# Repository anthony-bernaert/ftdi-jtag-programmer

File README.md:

# FTDI-based JTAG Programmer for FPGAs
This JTAG programmer board is based on an FTDI chip and supports Lattice, AMD (Xilinx), Intel (Altera) FPGAs, and probably more. It allows those devices to be programmed and debugged over USB through their regular toolchains.

The board also provides a separate UART port for general-purpose serial communication between a PC application and any other board.

If you work with a lot of different FPGAs, this solution can be used as a universal, cost-effective replacement for most of your vendor-specific JTAG cables.

## Features
- Based on the FT2232H chip
- USB-C connector
- On-board resettable fuse to protect your host's USB port
- 1 JTAG port
  - Programs and debugs Lattice, AMD/Xilinx, Altera/Intel, and probably also other FPGAs through their respective toolchains
  - Standard 2 mm Xilinx 2x7 header connector
  - Also has a 6-pin 2.54 mm header for use with jumper wires
  - Voltage reference input pin configures the I/O voltage (2.5-5V)
  - An LED indicates presence of an external VREF voltage
- 1 UART port
  - Generic serial communication through virtual COM port
  - 6-pin 2.54 mm header, pinout compatible with FTDI's TTL-232R cables
  - Configurable 5V output or voltage reference input (2.5-5V) (*)
  - An LED indicates presence of an external VREF voltage
- Buffered I/O pins with surge protection
  - Outputs are current-limited
  - Inputs are 5V tolerant
- For Xilinx/AMD and Lattice, only the standard FTDI software drivers are needed
 
(*) These are mounting variations, so to be decided during PCB assembly.

## Build overview

This board was designed using KiCad 7.0.2.

Navigate to the releases section to obtain the latest production files and schematic. The BOM contains references to LCSC parts, so that you can easily order PCB assemblies at e.g. JLCPCB.

Files for 3D printing an optional enclosure are also provided. The enclosure is recommended to prevent accidental shorts during use.

It consists of a top and bottom part, which slide in horizontally; no screws or glue are necessary. For resilience and visibility of the LEDs, it is recommended to print it in a translucent PETG material.

## How to use
### First-time configuration
Install FTDI's VCP/D2XX drivers for your operating system [from their website](https://ftdichip.com/drivers/).

Also install [FT_PROG](https://ftdichip.com/utilities/#ft_prog). This utility will be used to initialize the EEPROM of the board with the correct settings.

Now you can choose to either initialize the EEPROM using FT_PROG or directly flash the device using an existing EEPROM dump.

>[!TIP]
>The most versatile solution is to flash the EEPROM with the Digilent SMT1 dump. The programmer then works simultaneously for Vivado, ISE, Diamond and Quartus (details in the [Xilinx ISE section](#xilinx-ise)).
>
>However, for the very first startup of your board, please try to write the following settings using the FT_PROG utility. This way, you can make sure that your hardware and drivers are working properly.

When FT_PROG is installed, connect the board to your PC. At this point, the green PWREN LED should be on: this means the PC has enumerated the device. If this is not the case, see the [Troubleshooting Guide](TROUBLESHOOTING.md).

In FT_PROG, scan and parse the connected devices. Configure your board as follows:
- Port A
  - Set the hardware mode to "245 FIFO"
  - Set the driver to D2XX Direct
- Port B
  - Set the hardware mode to "RS232 UART"
  - Set the driver to Virtual COM Port

Finally, program this configuration into the EEPROM. Depending on the vendor of the FPGA you want to program, a few additional steps might be needed. These are described below.

### Lattice
To use the programmer with Lattice devices, just open the programming software such as Diamond Programmer and select the 'HW-USBN-2B (FTDI)' option as the cable type.

Diamond programmer can use any FTDI device configured in D2XX mode. No additional configuration is needed.

>[!NOTE]
>This programmer is known to work with Diamond Programmer software - other tools, such as Radiant Programmer, have not been tested yet.

### AMD/Xilinx Vivado
For AMD/Xilinx tools, the software looks for a Xilinx signature in the FTDI device EEPROM. Once this is done, the programmer appears as any other official programming cable in Vivado Hardware Manager. To add the signature, you have two options: either write a recognized EEPROM dump to the device (recommended), or use AMD's `program_ftdi` utility.

The recommended way is to use the Digilent SMT1 dump; refer to the [Xilinx ISE section](#xilinx-ise) on how to do this.

If you really want to do it AMD's way: recent Vivado versions (starting from 2022) contain the `program_ftdi` tool that configures FTDI chips as AMD/Xilinx JTAG programmers. Running this utility (once) will make the programmer work with Vivado. You can execute it from the TCL console, e.g. in the Hardware Manager of Vivado. Run a command similar to this one:
```
program_ftdi -write -ftdi FT2232H -serial 0ABC01 -vendor "my vendor co" -board "my board" -desc "my product desc"
```
Note that the 'serial' parameter must match the serial number generated by FT_PROG. After programming, the programmer should show up in the Hardware Manager of Vivado.

>[!WARNING]
>Unfortunately, it seems that the `program_ftdi` is broken in Vivado 2024.1. If you see it complaining about missing DLLs while trying to program, try using an older version of Vivado, e.g. 2023.2, which is known to work.

### Xilinx ISE
To use this programmer with Xilinx' older ISE toolchain, you'll need to flash the EEPROM to mimick a legacy Digilent SMT1 device. You will find the required EEPROM dump on [dragonlock2's ftdi_dumps repository](https://github.com/dragonlock2/ftdi_dumps?tab=readme-ov-file). Afterwards, the device appears as a Digilent SMT1 device in the cable setup window.

Note that this dump has the advantage that you can make the programmer work simultaneously for Vivado, ISE, Diamond and Quartus, turning your programmer in an (at least) 4-in-1 solution!

>[!TIP]
>Writing the EEPROM configuration can be done using the (Linux) utility `ftdi_eeprom` or my own [FTDI EEPROM cloning tool](https://github.com/anthony-bernaert/ftdi-cloner).

Once the EEPROM is programmed, the cable appears as a Digilent USB JTAG cable:

### Altera/Intel
For Quartus software to work with FT2232HL devices, one option is to add a library file to your Quartus installation directory. You'll find a ready-made DLL (if you're on Windows) [here](https://github.com/anthony-bernaert/jtag-mpsse-blaster). This is a fork of an open-source solution that adds FTDI MPSSE support to Quartus Programmer/Signal Tap. Linux is also supported, though I did not test this.

After installing the .dll/.so file, the JTAG programmer board should show up in the available hardware list of Quartus and your FPGA is ready to be programmed:

If you don't like modifying your Quartus installation manually, an alternative solution is to configure the USB device as an 'Arrow USB Blaster'. You will find the required EEPROM dump on [dragonlock2's ftdi_dumps repository](https://github.com/dragonlock2/ftdi_dumps?tab=readme-ov-file).

>[!TIP]
>Writing the EEPROM configuration can be done using the (Linux) utility `ftdi_eeprom` or my own [FTDI EEPROM cloning tool](https://github.com/anthony-bernaert/ftdi-cloner).

In this case, you also need to install the [Arrow USB Blaster driver](https://shop.trenz-electronic.de/en/Download/?path=Trenz_Electronic/Software/Drivers/Arrow_USB_Programmer). After this, your FTDI programmer should appear in the hardware list of Quartus Programmer and your FPGA is ready to be programmed.

## Troubleshooting
If you experience problems while using this board, check out the [Troubleshooting Guide](TROUBLESHOOTING.md).

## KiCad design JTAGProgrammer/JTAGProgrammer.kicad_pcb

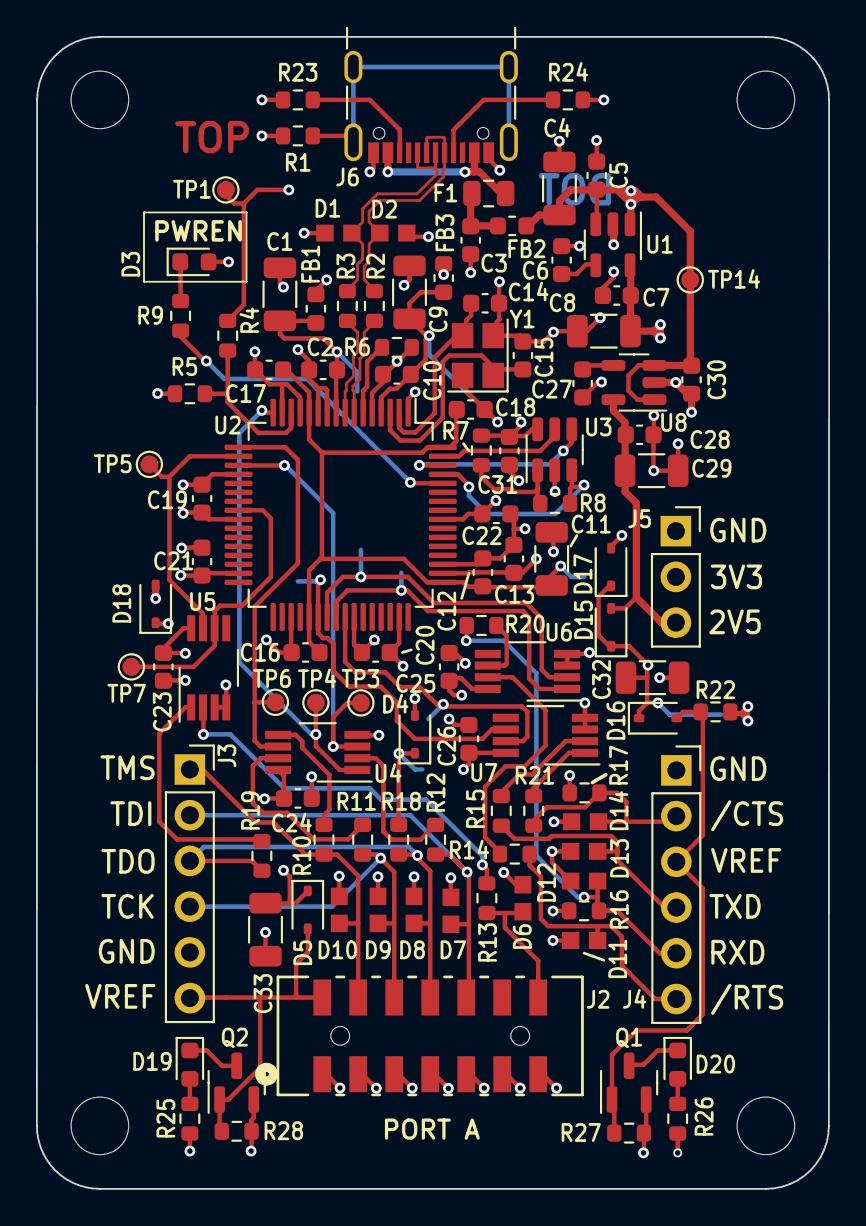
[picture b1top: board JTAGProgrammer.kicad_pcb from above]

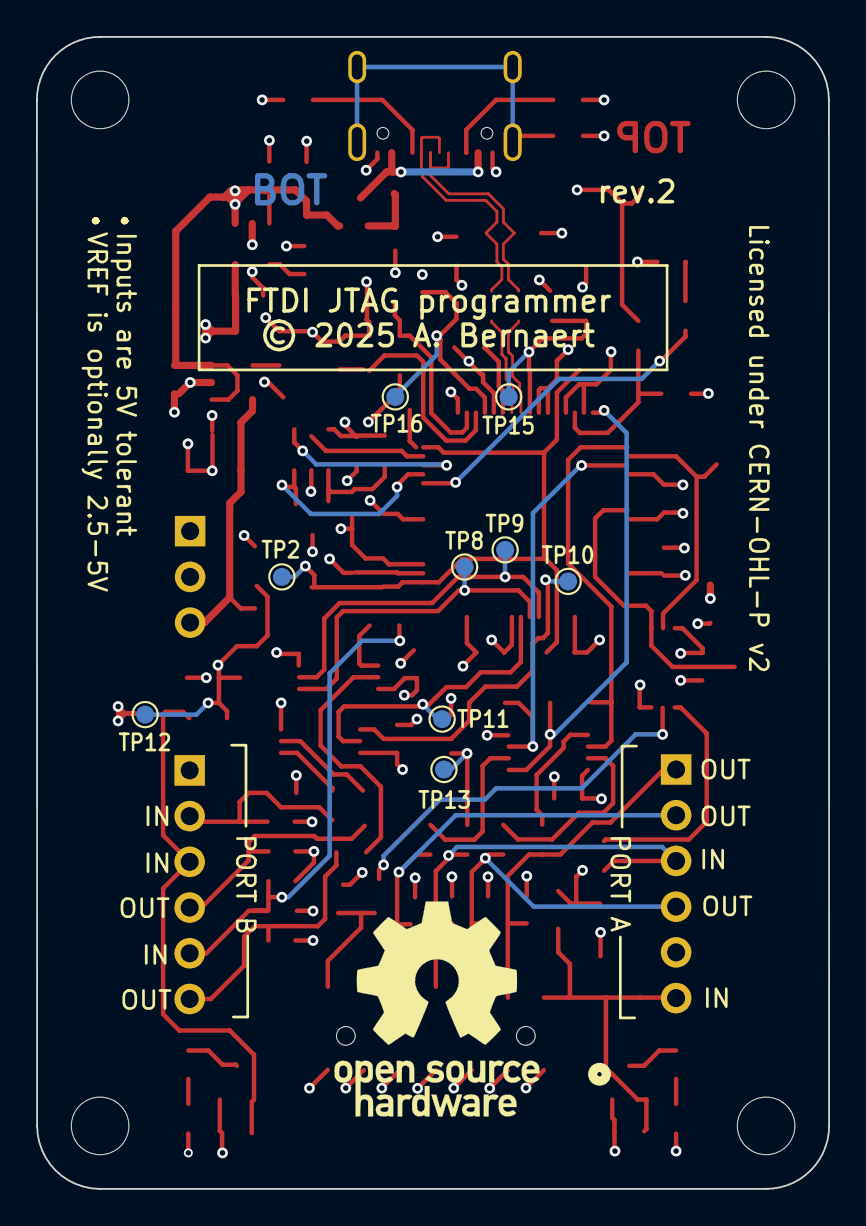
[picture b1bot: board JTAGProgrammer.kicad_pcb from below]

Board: 4 copper layers, 44.0 x 64.0 mm, 121 parts (9 on the bottom side), 63 nets.

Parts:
C1, C4, C8, C9, C11, C29, C32, C33: 4.7u; C_1206_3216Metric
C2, C5, C7, C10, C12, C13, C16, C17, C18, C19, C20, C21, C22, C23, C24, C25, C26, C28, C30, C31: 100n; C_0603_1608Metric
C3, C6, C27: 10n; C_0603_1608Metric
C14, C15: 10p; C_0603_1608Metric
D1, D2, D6, D7, D8, D9, D10, D11, D12, D13, D14: PGB1010603MR; DIOC1608X36N
D3, D19, D20: LED; LED_0603_1608Metric
D4, D5, D15, D16, D17, D18: CUS520,H3F; D_SOD-323
F1: 0805L075SLYR; Fuse_0805_2012Metric
FB1, FB2, FB3: BLM18AG601SN1D; L_0603_1608Metric
H1, H2, H3, H4: MountingHole; MountingHole_3.2mm_M3
J2: 878325623; CONN_87832-5623_MOL
J3, J4: Conn_01x06; PinSocket_1x06_P2.54mm_Vertical
J5: Conn_01x03; PinSocket_1x03_P2.54mm_Vertical
J6: USB_C_Receptacle_USB2.0; USB_C_Receptacle_GCT_USB4105-xx-A_16P_TopMnt_Horizontal
Q1, Q2: BSS123; SOT-23
R1, R22: 0R; R_0603_1608Metric
R2, R3: 10R; R_0603_1608Metric
R4: 15K; R_0603_1608Metric
R5, R7, R16, R17, R18, R27, R28: 10K; R_0603_1608Metric
R6: 12K; R_0603_1608Metric
R8: 2.2K; R_0603_1608Metric
R9, R25, R26: 100R; R_0603_1608Metric
R10, R11, R12, R13, R14, R15, R19, R20, R21: 150R; R_0603_1608Metric
R23, R24: 5K1; R_0603_1608Metric
TP1, TP2, TP3, TP4, TP5, TP6, TP7, TP8, TP9, TP10, TP11, TP12, TP13, TP14, TP15, TP16: TestPoint; TestPoint_Pad_D1.0mm
U1: LP2985-3.3; SOT-23-5
U2: FT2232HL; LQFP-64_10x10mm_P0.5mm
U3: 93LC56B; SOT-23-6
U4, U5, U6, U7: 74LVC3G17; VSSOP-8_3.0x3.0mm_P0.65mm
U8: LP2985-2.5; SOT-23-5
Y1: RH100-12.000-10-3030-TR; Crystal_SMD_3225-4Pin_3.2x2.5mm

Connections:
+1V8: C11.1, C12.1, C16.1, C17.1, C18.1, TP2.1, U2.12 (VCORE), U2.37 (VCORE), U2.49 (VREGOUT), U2.64 (VCORE)
+2V5: C28.1, C29.1, D4.2 (A), D15.2 (A), J5.3, U8.5 (VOUT)
+3V3: C7.1, C8.1, C13.1, C19.1, C20.1, C21.1, C22.1, C31.1, D3.2 (A), D17.2 (A), D18.2 (A), FB1.1, FB3.1, J5.2, R7.2, R25.1, R26.1, U1.5 (VOUT), U2.20 (VCCIO), U2.31 (VCCIO), U2.42 (VCCIO), U2.50 (VREGIN), U2.56 (VCCIO), U3.6 (VCC)
/FTDI/FTDI_D+: R3.2, U2.8 (DP)
/FTDI/FTDI_D-: R2.2, U2.7 (DM)
/FTDI/JTAG_SRST: TP7.1, U2.24 (ADBUS7), U5.6
/FTDI/JTAG_TCK: TP4.1, U2.16 (ADBUS0), U4.1
/FTDI/JTAG_TDI: TP6.1, U2.17 (ADBUS1), U4.6
/FTDI/JTAG_TDO: TP5.1, U2.18 (ADBUS2), U5.7
/FTDI/JTAG_TMS: TP3.1, U2.19 (ADBUS3), U4.3
/FTDI/UART_CTS: TP11.1, U2.41 (BDBUS3), U7.7
/FTDI/UART_RTS: TP8.1, U2.40 (BDBUS2), U6.1
/FTDI/UART_RXD: TP9.1, U2.39 (BDBUS1), U6.2
/FTDI/UART_TXD: TP10.1, U2.38 (BDBUS0), U7.6
/FTDI/VPHY: C9.1, C10.1, FB3.2, TP16.1, U2.4 (VPHY)
/FTDI/VPLL: C1.1, C2.1, FB1.2, TP15.1, U2.9 (VPLL)
/JTAG/SRST_BUF: D6.1, J2.14, R13.2
/JTAG/TCK_BUF: D9.1, J2.6, J3.4, R11.2
/JTAG/TDI_BUF: D7.1, J2.10, J3.2, R12.2
/JTAG/TDO_CONN: D8.1, J2.8, J3.3, R18.1, R19.2
/JTAG/TMS_BUF: D10.1, J2.4, J3.1, R10.2
/JTAG/VIO_JTAG: C23.1, C24.1, C33.1, D4.1 (K), D5.1 (K), D18.1 (K), R18.2, TP13.1, U4.8 (VCC), U5.8 (VCC)
/JTAG/VREF: D5.2 (A), J2.2, J3.6, Q2.1 (G), R28.2
/Power/VBUS: F1.1, J6.A4 (VBUS), J6.A9 (VBUS), J6.B4 (VBUS), J6.B9 (VBUS)
/UART/CTS_CONN: D14.1, J4.2, R17.1, R21.2
/UART/RTS_BUF: D11.1, J4.6, R14.2
/UART/RXD_CONN: D12.1, J4.5, R16.1, R20.2
/UART/TXD_BUF: D13.1, J4.4, R15.2
/UART/VIO_UART: C25.1, C26.1, C32.1, D15.1 (K), D16.1 (K), D17.1 (K), R16.2, R17.2, TP12.1, U6.8 (VCC), U7.8 (VCC)
/UART/VREF_CONN: D16.2 (A), J4.3, Q1.1 (G), R22.2, R27.2
/USB_D+: D1.1, J6.A6 (D+), J6.B6 (D+), R3.1
/USB_D-: D2.1, J6.A7 (D-), J6.B7 (D-), R2.1
/USB_SHIELD: J6.S1 (SHIELD), R1.1
/VBUS_FILT: C4.1, C5.1, C30.1, FB2.2, R4.1, R22.1, TP1.1, TP14.1, U1.1 (VIN), U1.3 (ON/~OFF), U8.1 (VIN), U8.3 (ON/~OFF)
GND: C1.2, C2.2, C3.2, C4.2, C5.2, C6.2, C7.2, C8.2, C9.2, C10.2, C11.2, C12.2, C13.2, C14.2, C15.2, C16.2, C17.2, C18.2, C19.2, C20.2, C21.2, C22.2, C23.2, C24.2, C25.2, C26.2, C27.2, C28.2, C29.2, C30.2, C31.2, C32.2, C33.2, D1.2, D2.2, D6.2, D7.2, D8.2, D9.2, D10.2, D11.2, D12.2, D13.2, D14.2, J2.1, J2.3, J2.5, J2.7, J2.9, J2.11, J2.13, J3.5, J4.1, J5.1, J6.A1 (GND), J6.A12 (GND), J6.B1 (GND), J6.B12 (GND), Q1.2 (S), Q2.2 (S), R1.2, R5.1, R6.1, R23.2, R24.2, R27.1, R28.1, U1.2 (GND), U2.1 (GND), U2.5 (GND), U2.10 (AGND), U2.11 (GND), U2.13 (TEST), U2.15 (GND), U2.25 (GND), U2.35 (GND), U2.47 (GND), U2.51 (GND), U3.2 (GND), U4.4 (GND), U5.3, U5.4 (GND), U6.3, U6.4 (GND), U7.3, U7.4 (GND), U8.2 (GND), Y1.2, Y1.4
unnamed: C3.1, F1.2, FB2.1
unnamed: D3.1 (K), R9.2
unnamed: D19.2 (A), R25.2
unnamed: D19.1 (K), Q2.3 (D)
unnamed: D20.2 (A), R26.2
unnamed: D20.1 (K), Q1.3 (D)
unnamed: J6.A5 (CC1), R24.1
unnamed: J6.B5 (CC2), R23.1
unnamed: R10.1, U4.5
unnamed: R11.1, U4.7
unnamed: R12.1, U4.2
unnamed: R13.1, U5.2
unnamed: R14.1, U6.7
unnamed: R15.1, U7.2
unnamed: R19.1, U5.1
unnamed: R20.1, U6.6
unnamed: R21.1, U7.1
unnamed: C6.1, U1.4 (BP)
unnamed: U2.62 (EECLK), U3.4 (CLK)
unnamed: U2.63 (EECS), U3.5 (CS)
unnamed: R8.2, U2.61 (EEDATA), U3.3 (DI)
unnamed: C14.1, U2.2 (OSCI), Y1.3
unnamed: C15.1, U2.3 (OSCO), Y1.1
unnamed: R6.2, U2.6 (REF)
unnamed: R9.1, U2.60 (~PWREN)
unnamed: R4.2, R5.2, U2.14 (~RESET)
unnamed: R7.1, R8.1, U3.1 (DO)
unnamed: C27.1, U8.4 (BP)

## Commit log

2024-10-06 Add license
2024-11-03 Check-in of revision 1
2024-11-06 Add USB driver conflict to troubleshooting guide
2024-11-07 Updated README on ISE compatibility
2024-11-12 Update troubleshooting guide (EEPROM corruption)
2024-11-12 Update README screenshots
2024-11-13 Add LCSC part numbers
2024-11-13 Fix wrong comment in schematic on UART VREF/5V mounting options
2024-11-16 Update README: add pictures and links to FTDI cloner
2024-11-16 Resize pictures in README
2024-11-24 Update README, add Quartus MPSSE description
2024-12-28 Add Quartus JTAG MPSSE screenshot
2025-06-03 Add enclosure design file
2025-06-03 Rev.2: change to USB Type-C, add VBUS fuse, VREF LED indicators
2025-06-03 Update README for rev 2

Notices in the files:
JTAGProgrammer/JTAGProgrammer.kicad_pcb:
Licensed under CERN-OHL-P v2
© 2025 A. Bernaert
